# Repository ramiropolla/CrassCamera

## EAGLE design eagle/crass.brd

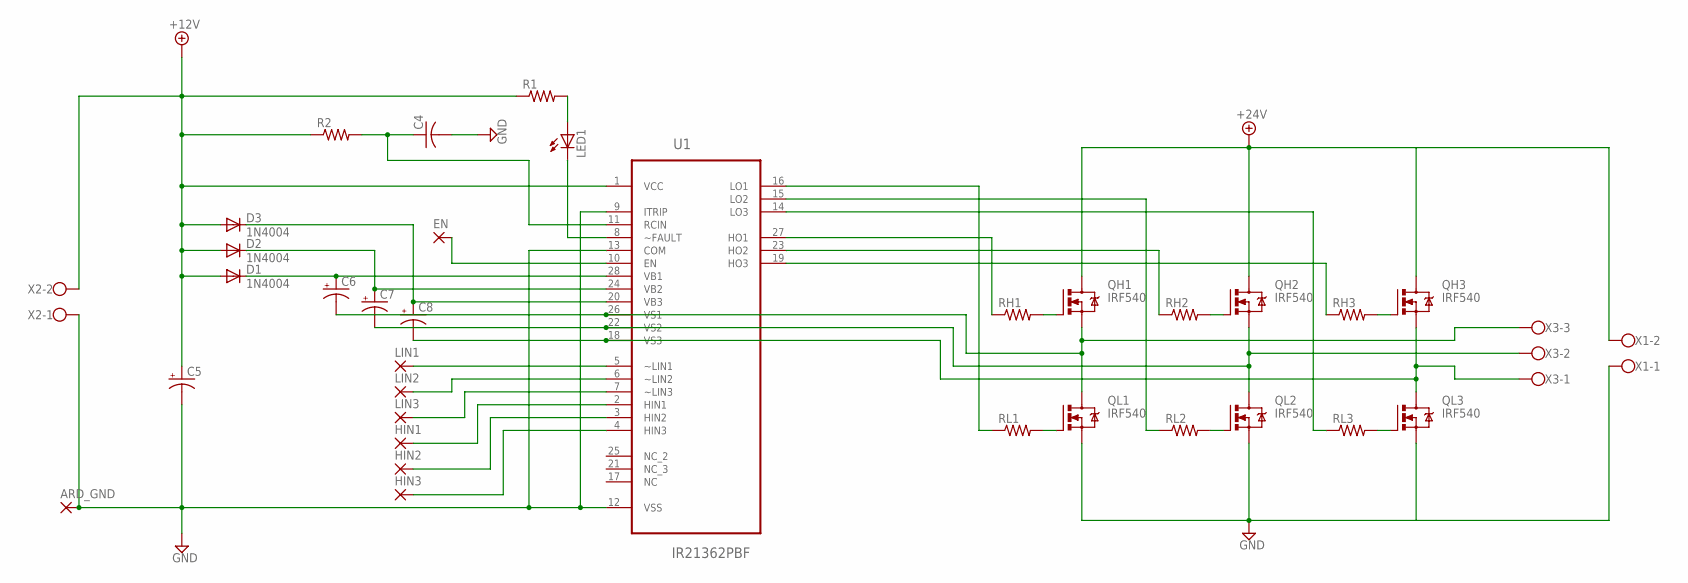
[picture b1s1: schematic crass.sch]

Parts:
ARD_GND: 2,54/1,0
C4: C-US025-025X050; C025-025X050
C5: CPOL-USE2.5-7; E2,5-7
C6, C7, C8: CPOL-USE2.5-5; E2,5-5
D1, D2, D3: 1N4004; DO41-10
EN: 2,54/1,0
HIN1, HIN2, HIN3: 2,54/1,0
LED1: LED5MM
LIN1, LIN2, LIN3: 2,54/1,0
QH1, QH2, QH3: IRF540; TO220BV
QL1, QL2, QL3: IRF540; TO220BV
R1, R2: R-US_0204/7; 0204/7
RH1, RH2, RH3: R-US_0204/7; 0204/7
RL1, RL2, RL3: R-US_0204/7; 0204/7
U1: IR21362PBF; DIP254P1524X635-28
X1, X2: W237-102
X3: W237-103

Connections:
+12V: C5.+, D1.A, D2.A, D3.A, R1.1, R2.1, U1.1 (VCC), X2.2
+24V: QH1.D, QH2.D, QH3.D, X1.2
GND: ARD_GND.1, C4.2, C5.-, QL1.S, QL2.S, QL3.S, U1.9 (ITRIP), U1.12 (VSS), U1.13 (COM), X1.1, X2.1
LIN2: LIN1.1, U1.5 (~LIN1)
unnamed: C6.+, D1.C, U1.28 (VB1)
unnamed: C6.-, QH1.S, QL1.D, U1.26 (VS1), X3.3
unnamed: C7.+, D2.C, U1.24 (VB2)
unnamed: C7.-, QH2.S, QL2.D, U1.22 (VS2), X3.2
unnamed: C8.+, D3.C, U1.20 (VB3)
unnamed: C8.-, QH3.S, QL3.D, U1.18 (VS3), X3.1
unnamed: QH1.G, RH1.2
unnamed: LED1.A, R1.2
unnamed: LED1.K (C), U1.8 (~FAULT)
unnamed: C4.1, R2.2, U1.11 (RCIN)
unnamed: QL1.G, RL1.2
unnamed: QH2.G, RH2.2
unnamed: QL2.G, RL2.2
unnamed: QH3.G, RH3.2
unnamed: QL3.G, RL3.2
unnamed: RH1.1, U1.27 (HO1)
unnamed: RL1.1, U1.16 (LO1)
unnamed: RH2.1, U1.23 (HO2)
unnamed: RH3.1, U1.19 (HO3)
unnamed: RL2.1, U1.15 (LO2)
unnamed: RL3.1, U1.14 (LO3)
unnamed: EN.1, U1.10 (EN)
unnamed: LIN2.1, U1.6 (~LIN2)
unnamed: LIN3.1, U1.7 (~LIN3)
unnamed: HIN1.1, U1.2 (HIN1)
unnamed: HIN2.1, U1.3 (HIN2)
unnamed: HIN3.1, U1.4 (HIN3)

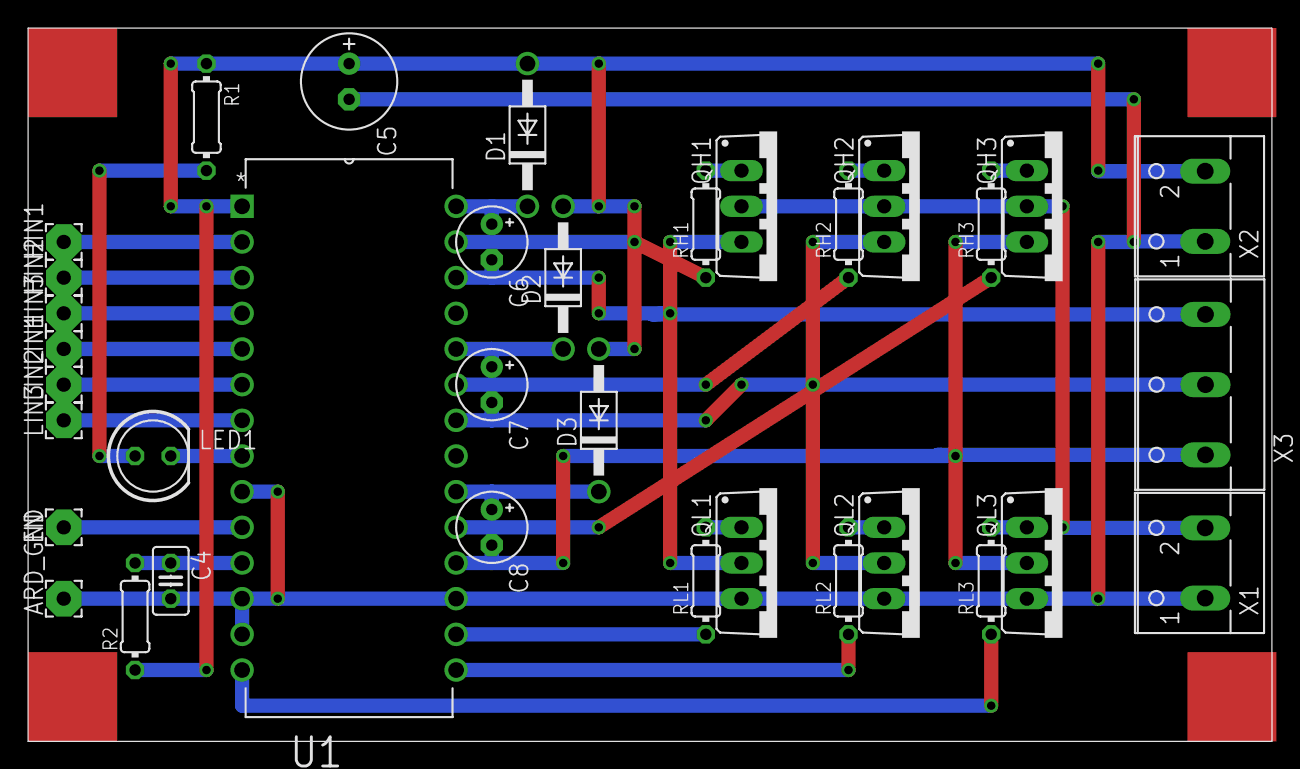
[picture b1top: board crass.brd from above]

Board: 2 copper layers, 88.6 x 50.8 mm, 35 parts (0 on the bottom side), 31 nets.

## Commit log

2015-01-18 Add initial documentation in PDF
    Obtained from http://www.filmlabs.org/index.php/technical-tips/crass/
2015-01-18 Initial CameraCrass.pdf transcription
2015-01-18 Fix typos, extra spaces, and remove line-wrapping hyphens
2015-01-18 Add line breaks and fix headings
2015-01-18 <72 columns
2015-01-18 Fix Title
2015-01-18 Initial unfinished Manual_Crass
2015-02-21 add kicad stuff
2015-07-19 arduino sketch
2015-07-19 eagle stuff
